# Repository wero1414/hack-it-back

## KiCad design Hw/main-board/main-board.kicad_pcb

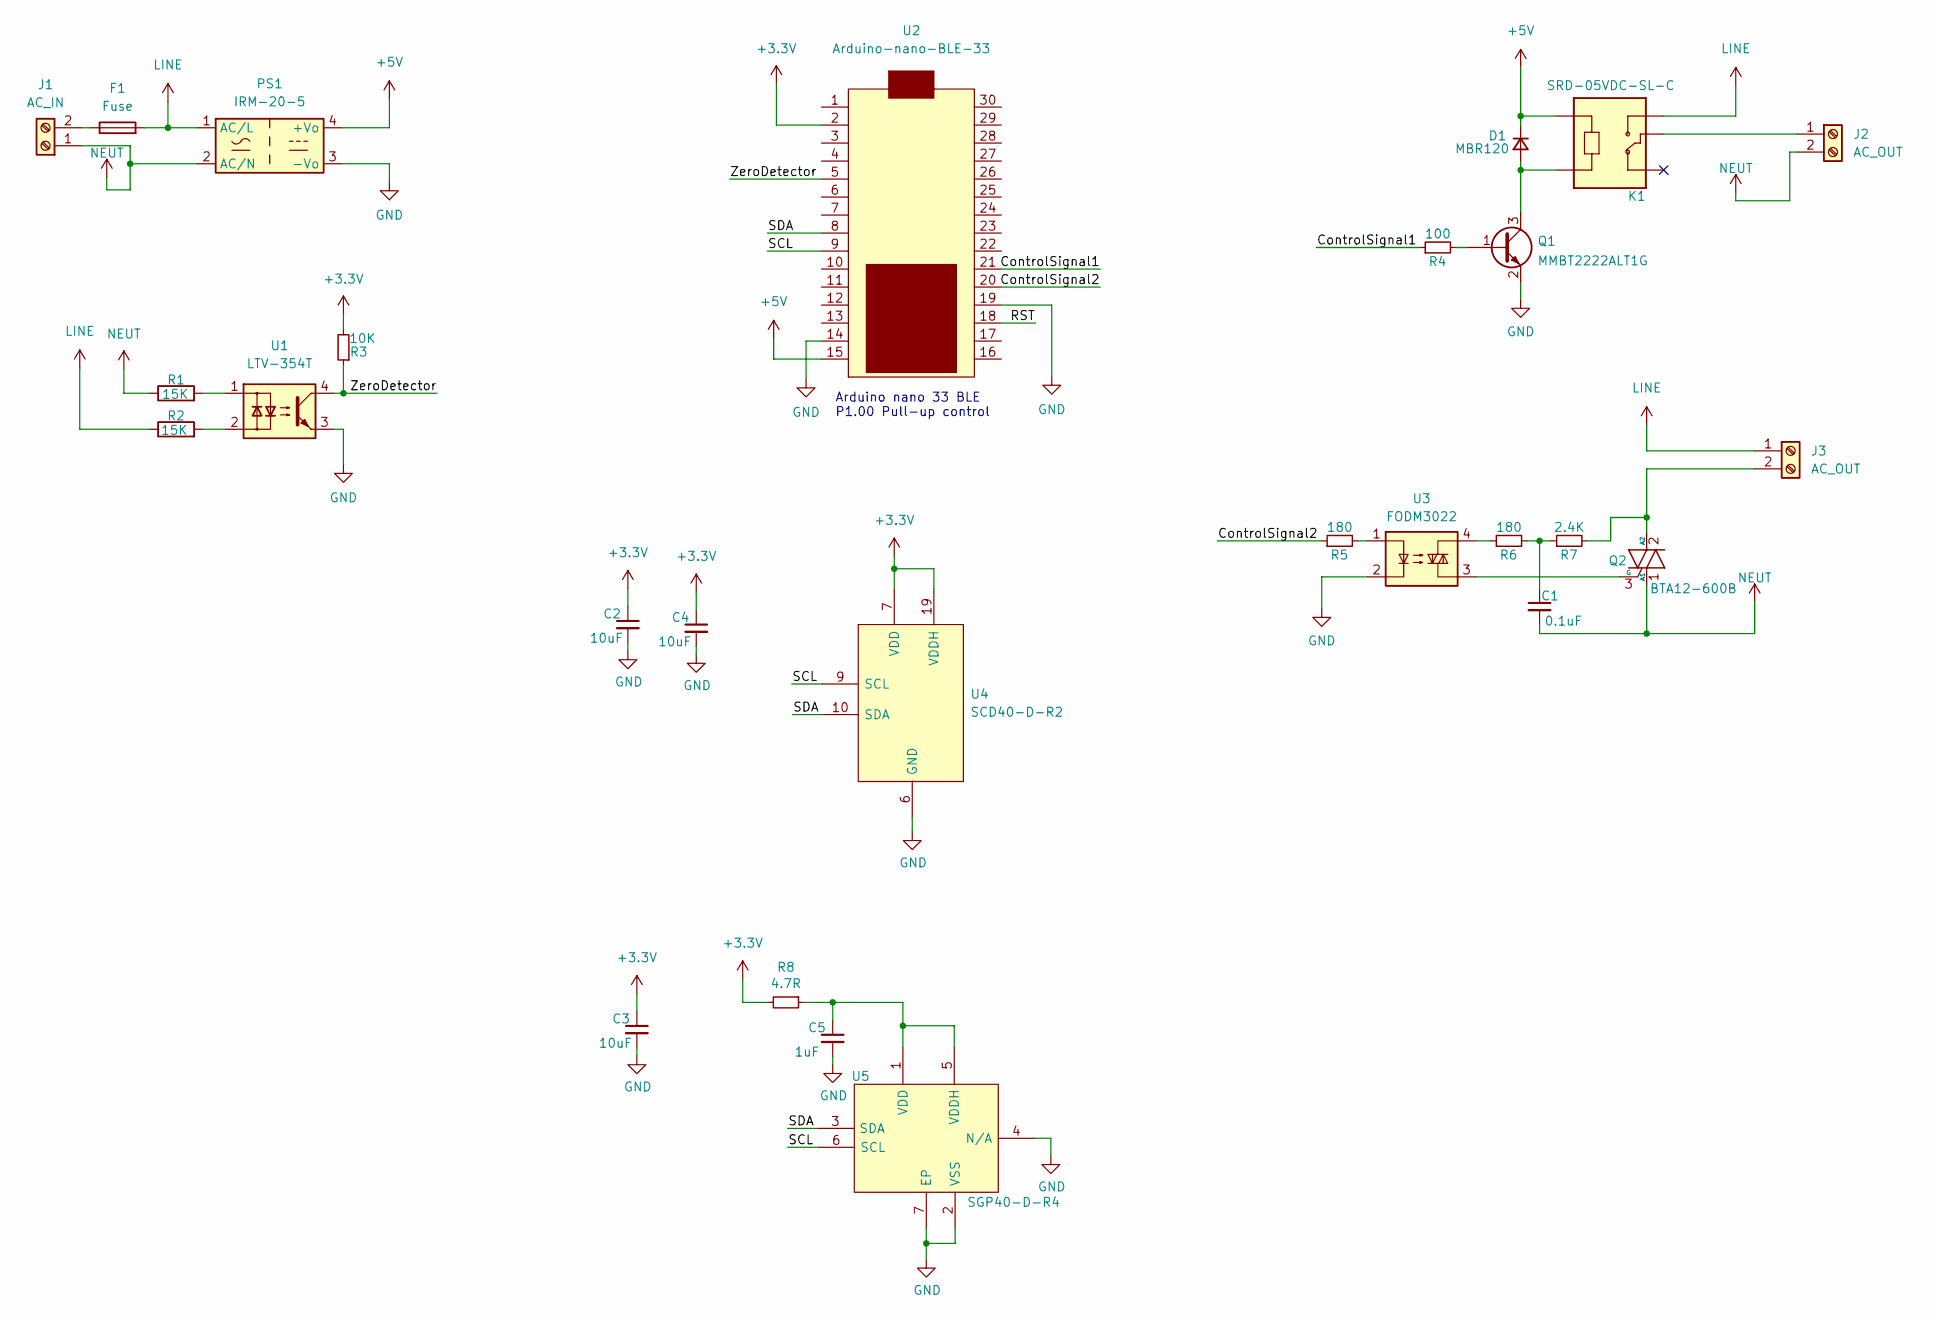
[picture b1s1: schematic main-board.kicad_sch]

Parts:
C1: 0.1uF; C_1206_3216Metric
C2, C3, C4: 10uF; C_0805_2012Metric
C5: 1uF; C_0805_2012Metric
D1: MBR120; D_SOD-123
F1: Fuse; Fuseholder_Littelfuse_100_series_5x20mm
J1: AC_IN; TerminalBlock_bornier-2_P5.08mm
J2, J3: AC_OUT; TerminalBlock_bornier-2_P5.08mm
K1: SRD-05VDC-SL-C; RELAY_SRD-05VDC-SL-C
PS1: IRM-20-5; Converter_ACDC_MeanWell_IRM-20-xx_THT
Q1: MMBT2222ALT1G; SOT-23
Q2: BTA12-600B; TO-220-3_Vertical
R1, R2: 15K; R_1206_3216Metric
R3: 10K; R_0805_2012Metric
R4: 100; R_0805_2012Metric
R5: 180; R_0805_2012Metric
R6: 180; R_1206_3216Metric
R7: 2.4K; R_1206_3216Metric
R8: 4.7R; R_0805_2012Metric
U1: LTV-354T; SO-4_4.4x3.6mm_P2.54mm
U2: Arduino-nano-BLE-33; NANO_33_Footprint_SMD_Castell
U3: FODM3022; SMDIP-4_W7.62mm
U4: SCD40-D-R2; SCD40DR2
U5: SGP40-D-R4; SON80P244X244X95-7N

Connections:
+3V3: C2.1, C3.1, C4.1, R3.2, R8.2, U2.2, U4.7 (VDD), U4.19 (VDDH)
+5V: D1.1 (K), K1.A1, PS1.4 (+Vo), U2.15
/ControlSignal1: R4.1, U2.21
/ControlSignal2: R5.1, U2.20
/RST: U2.18
/SCL: U2.9, U4.9 (SCL), U5.6 (SCL)
/SDA: U2.8, U4.10 (SDA), U5.3 (SDA)
/ZeroDetector: R3.1, U1.4, U2.5
GND: C2.2, C3.2, C4.2, C5.2, PS1.3 (-Vo), Q1.2 (E), U1.3, U2.14, U2.19, U3.2, U4.6 (GND), U4.20 (GND_2), U4.21 (GND_3), U5.2 (VSS), U5.4 (N/A), U5.7 (EP)
LINE: F1.2, J3.1, K1.NO, PS1.1 (AC/L), R2.1
NEUT: C1.2, J1.1, J2.2, PS1.2 (AC/N), Q2.1 (A1), R1.1
unnamed: C1.1, R6.2, R7.1
unnamed: C5.1, R8.1, U5.1 (VDD), U5.5 (VDDH)
unnamed: D1.2 (A), K1.A2, Q1.3 (C)
unnamed: F1.1, J1.2
unnamed: J2.1, K1.COM
unnamed: J3.2, Q2.2 (A2), R7.2
unnamed: Q1.1 (B), R4.2
unnamed: Q2.3 (G), U3.3
unnamed: R1.2, U1.1
unnamed: R2.2, U1.2
unnamed: R5.2, U3.1
unnamed: R6.1, U3.4

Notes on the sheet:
Arduino nano 33 BLE P1.00 Pull-up control

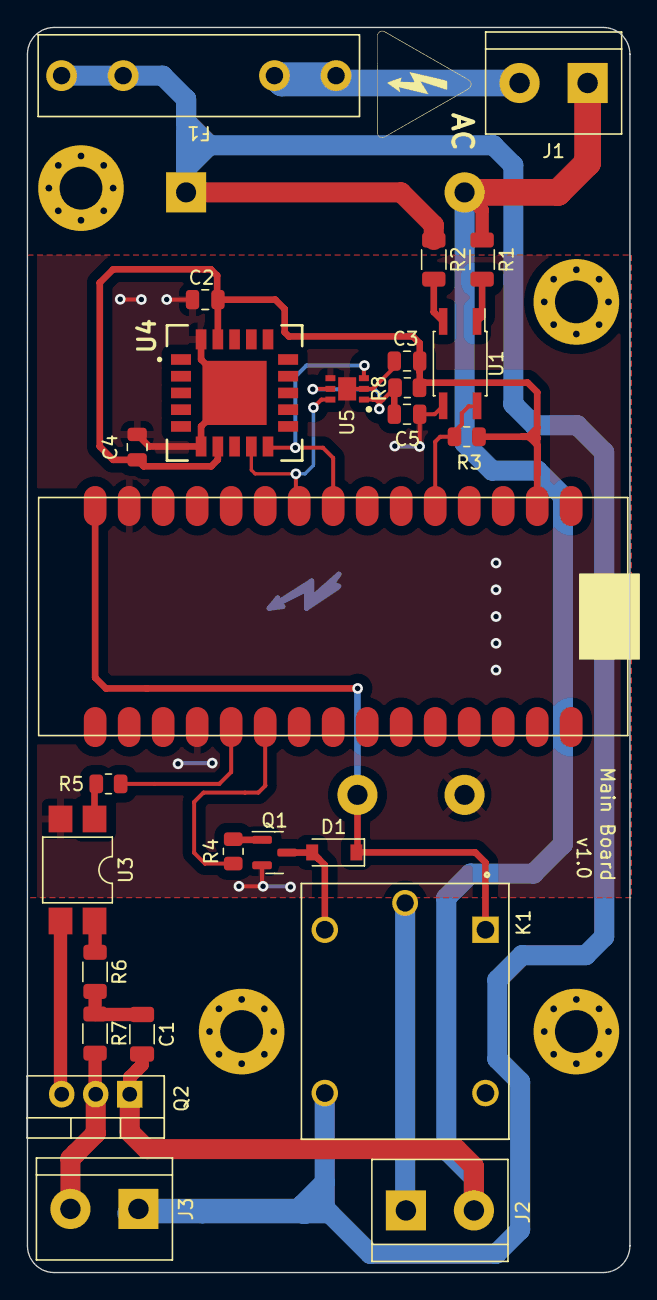
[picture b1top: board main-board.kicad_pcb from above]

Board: 2 copper layers, 45.0 x 93.0 mm, 27 parts (1 on the bottom side), 22 nets.

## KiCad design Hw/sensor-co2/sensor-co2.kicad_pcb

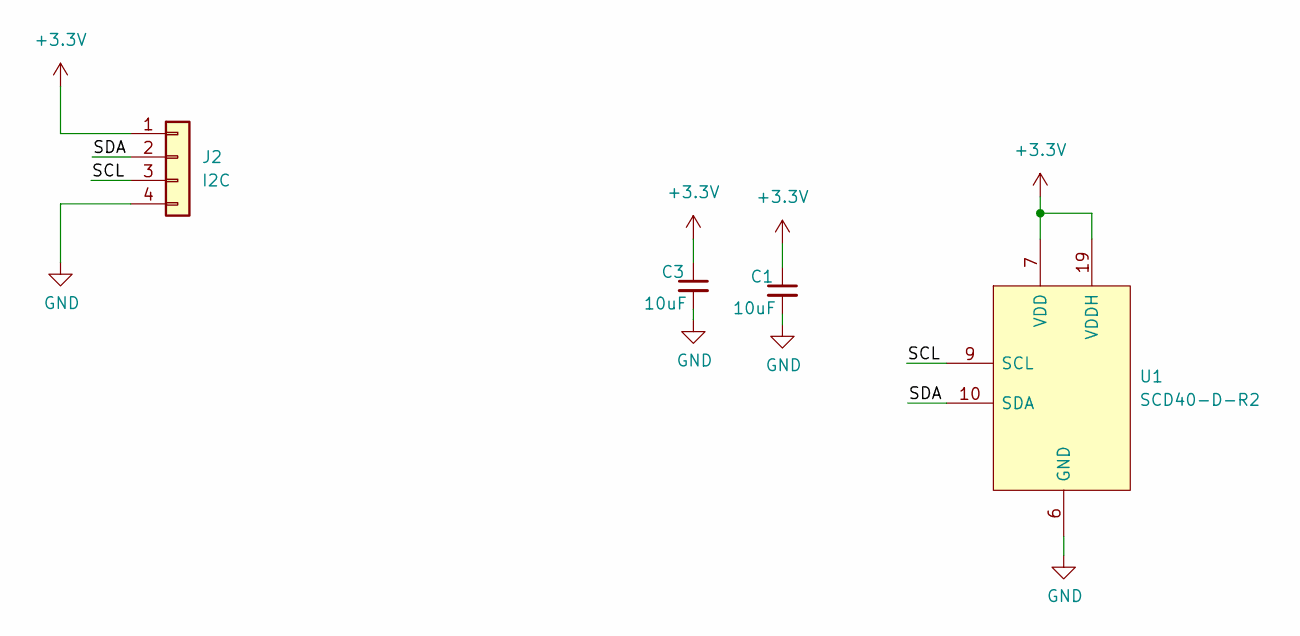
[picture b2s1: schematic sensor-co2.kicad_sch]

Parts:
C1, C3: 10uF; C_0805_2012Metric
J2: I2C; PinHeader_1x04_P2.54mm_Vertical
U1: SCD40-D-R2; SCD40DR2

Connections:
+3V3: C1.1, C3.1, J2.1, U1.7 (VDD), U1.19 (VDDH)
/SCL: J2.3, U1.9 (SCL)
/SDA: J2.2, U1.10 (SDA)
GND: C1.2, C3.2, J2.4, U1.6 (GND), U1.20 (GND_2), U1.21 (GND_3)

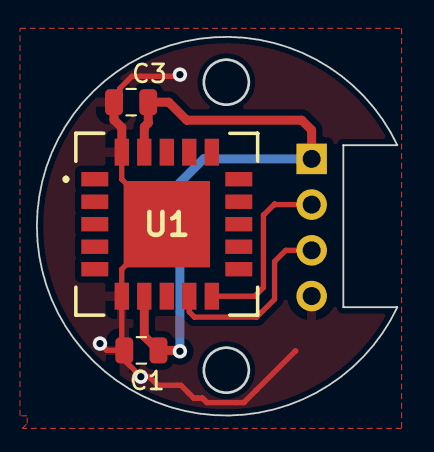
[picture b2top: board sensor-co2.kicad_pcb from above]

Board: 2 copper layers, 20.0 x 21.0 mm, 4 parts (1 on the bottom side), 4 nets.

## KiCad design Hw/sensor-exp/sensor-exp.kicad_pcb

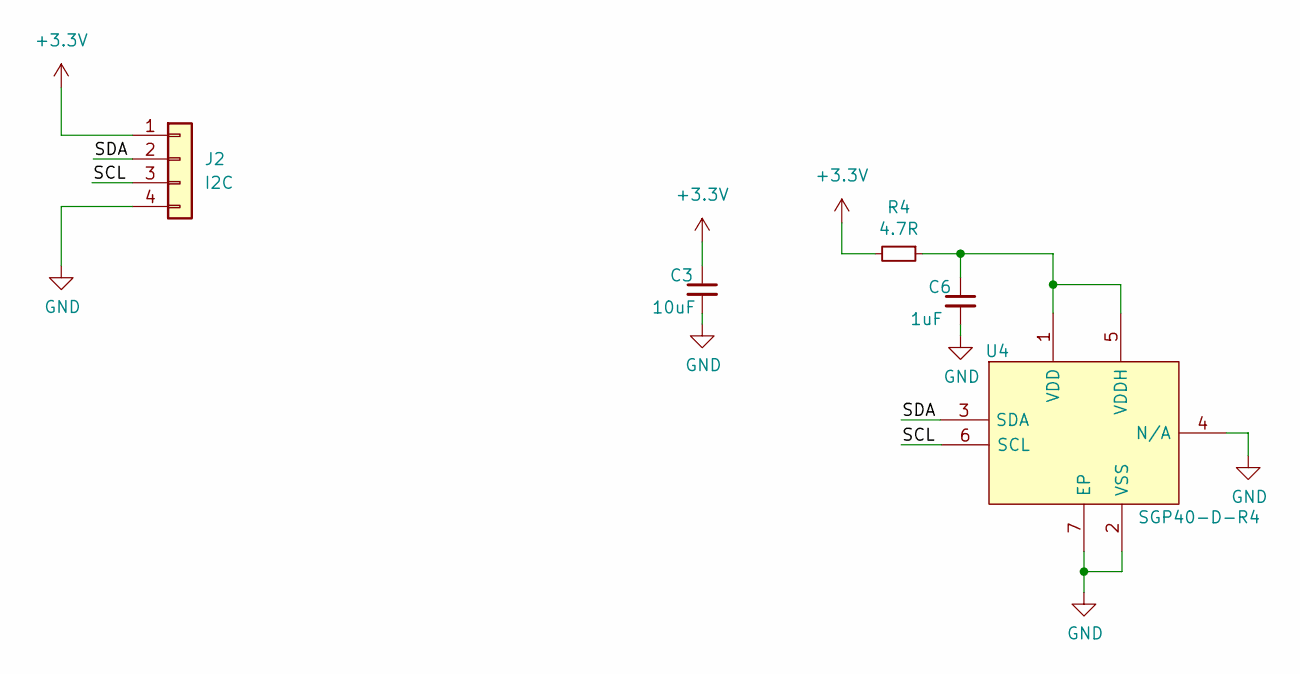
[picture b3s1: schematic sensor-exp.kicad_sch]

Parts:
C3: 10uF; C_0805_2012Metric
C6: 1uF; C_0805_2012Metric
J2: I2C; PinHeader_1x04_P2.54mm_Vertical
R4: 4.7R; R_0805_2012Metric
U4: SGP40-D-R4; SON80P244X244X95-7N

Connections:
+3V3: C3.1, J2.1, R4.2
/SCL: J2.3, U4.6 (SCL)
/SDA: J2.2, U4.3 (SDA)
GND: C3.2, C6.2, J2.4, U4.2 (VSS), U4.4 (N/A), U4.7 (EP)
unnamed: C6.1, R4.1, U4.1 (VDD), U4.5 (VDDH)

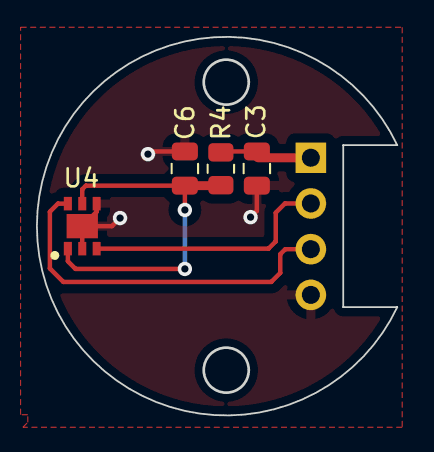
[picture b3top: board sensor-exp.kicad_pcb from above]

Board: 2 copper layers, 20.0 x 21.0 mm, 5 parts (1 on the bottom side), 5 nets.

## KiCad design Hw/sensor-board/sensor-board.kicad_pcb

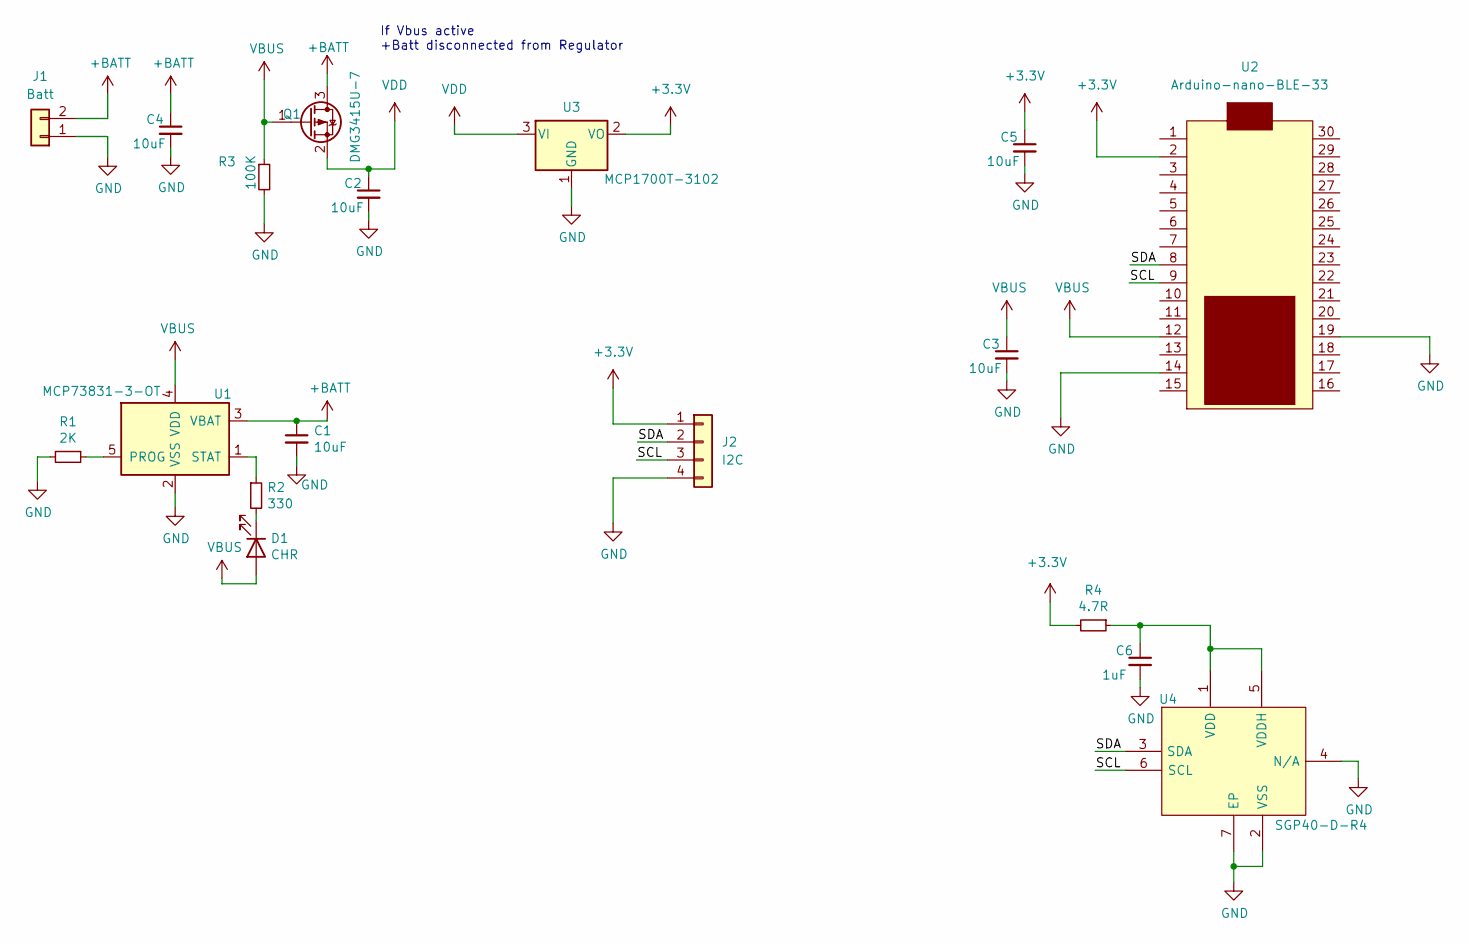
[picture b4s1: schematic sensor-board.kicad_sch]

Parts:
C1, C2, C3, C4, C5: 10uF; C_0805_2012Metric
C6: 1uF; C_0805_2012Metric
D1: CHR; LED_0805_2012Metric_Pad1.15x1.40mm_HandSolder
J1: Batt; PinHeader_1x02_P2.54mm_Vertical
J2: I2C; PinHeader_1x04_P2.54mm_Vertical
Q1: DMG3415U-7; SOT-23
R1: 2K; R_0805_2012Metric
R2: 330; R_0805_2012Metric
R3: 100K; R_0805_2012Metric
R4: 4.7R; R_0805_2012Metric
U1: MCP73831-3-OT; SOT-23-5
U2: Arduino-nano-BLE-33; NANO_33_Footprint_SMD_Castell
U3: MCP1700T-3102; SOT-23
U4: SGP40-D-R4; SON80P244X244X95-7N

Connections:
+3V3: C5.1, J2.1, R4.2, U2.2, U3.2 (VO)
+BATT: C1.1, C4.1, J1.2, Q1.3 (D), U1.3 (VBAT)
/SCL: J2.3, U2.9, U4.6 (SCL)
/SDA: J2.2, U2.8, U4.3 (SDA)
GND: C1.2, C2.2, C3.2, C4.2, C5.2, C6.2, J1.1, J2.4, R1.2, R3.2, U1.2 (VSS), U2.14, U2.19, U3.1 (GND), U4.2 (VSS), U4.4 (N/A), U4.7 (EP)
unnamed: C6.1, R4.1, U4.1 (VDD), U4.5 (VDDH)
unnamed: D1.1 (K), R2.2
unnamed: R1.1, U1.5 (PROG)
unnamed: R2.1, U1.1 (STAT)
VBUS: C3.1, D1.2 (A), Q1.1 (G), R3.1, U1.4 (VDD), U2.12
VDD: C2.1, Q1.2 (S), U3.3 (VI)

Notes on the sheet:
If Vbus active +Batt disconnected from Regulator

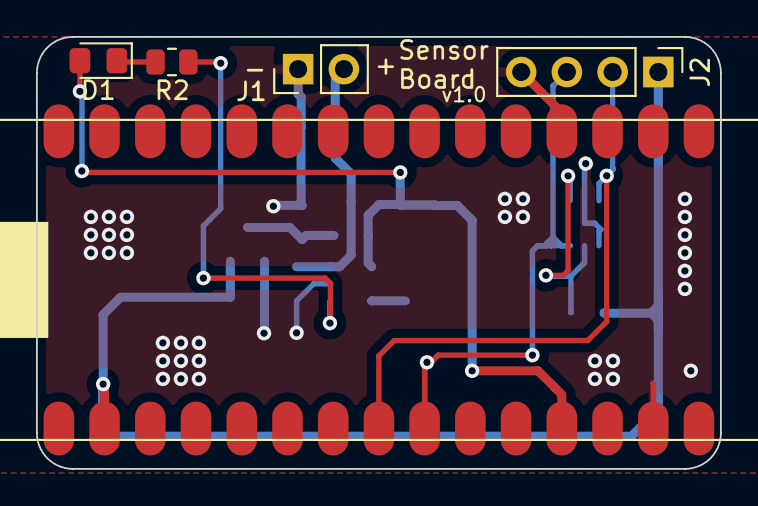
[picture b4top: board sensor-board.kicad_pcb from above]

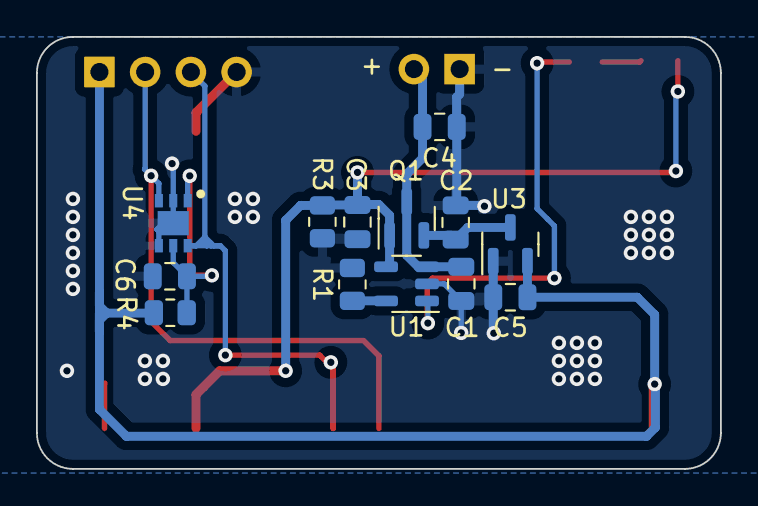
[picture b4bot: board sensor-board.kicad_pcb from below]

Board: 2 copper layers, 38.0 x 24.0 mm, 18 parts (13 on the bottom side), 11 nets.

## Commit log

2022-03-07 update gitignore
2022-03-07 add kicad projects
2022-03-07 update sensor board schematic
2022-03-14 update sensors and sensorBoard
2022-03-14 erase backups
2022-03-14 update pins sensor board
2022-03-14 update main board
2022-03-14 add step files
2022-03-23 add gerbers
2022-03-23 move to hardware folder
2022-04-23 update project add firmware
2022-04-23 update Kicad project
2022-04-23 add phase control
2022-04-28 change name add code
2022-04-28 update central address read
2022-04-28 erase test script
2022-04-28 add readings of BLE found bug
2022-05-04 update state
2022-05-04 sabas changes
2022-05-12 update to 1 connection
2022-05-13 modify debug mode
2022-05-13 add gitingnore
2022-05-13 update firmware
